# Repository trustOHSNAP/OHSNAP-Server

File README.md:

# OHSNAP Server
This is the repository for the OHSNAP Server project of the OHSNAP platform. For more information, see the [OHSNAP Wiki][https://www.noisebridge.net/wiki/OHSNAP].

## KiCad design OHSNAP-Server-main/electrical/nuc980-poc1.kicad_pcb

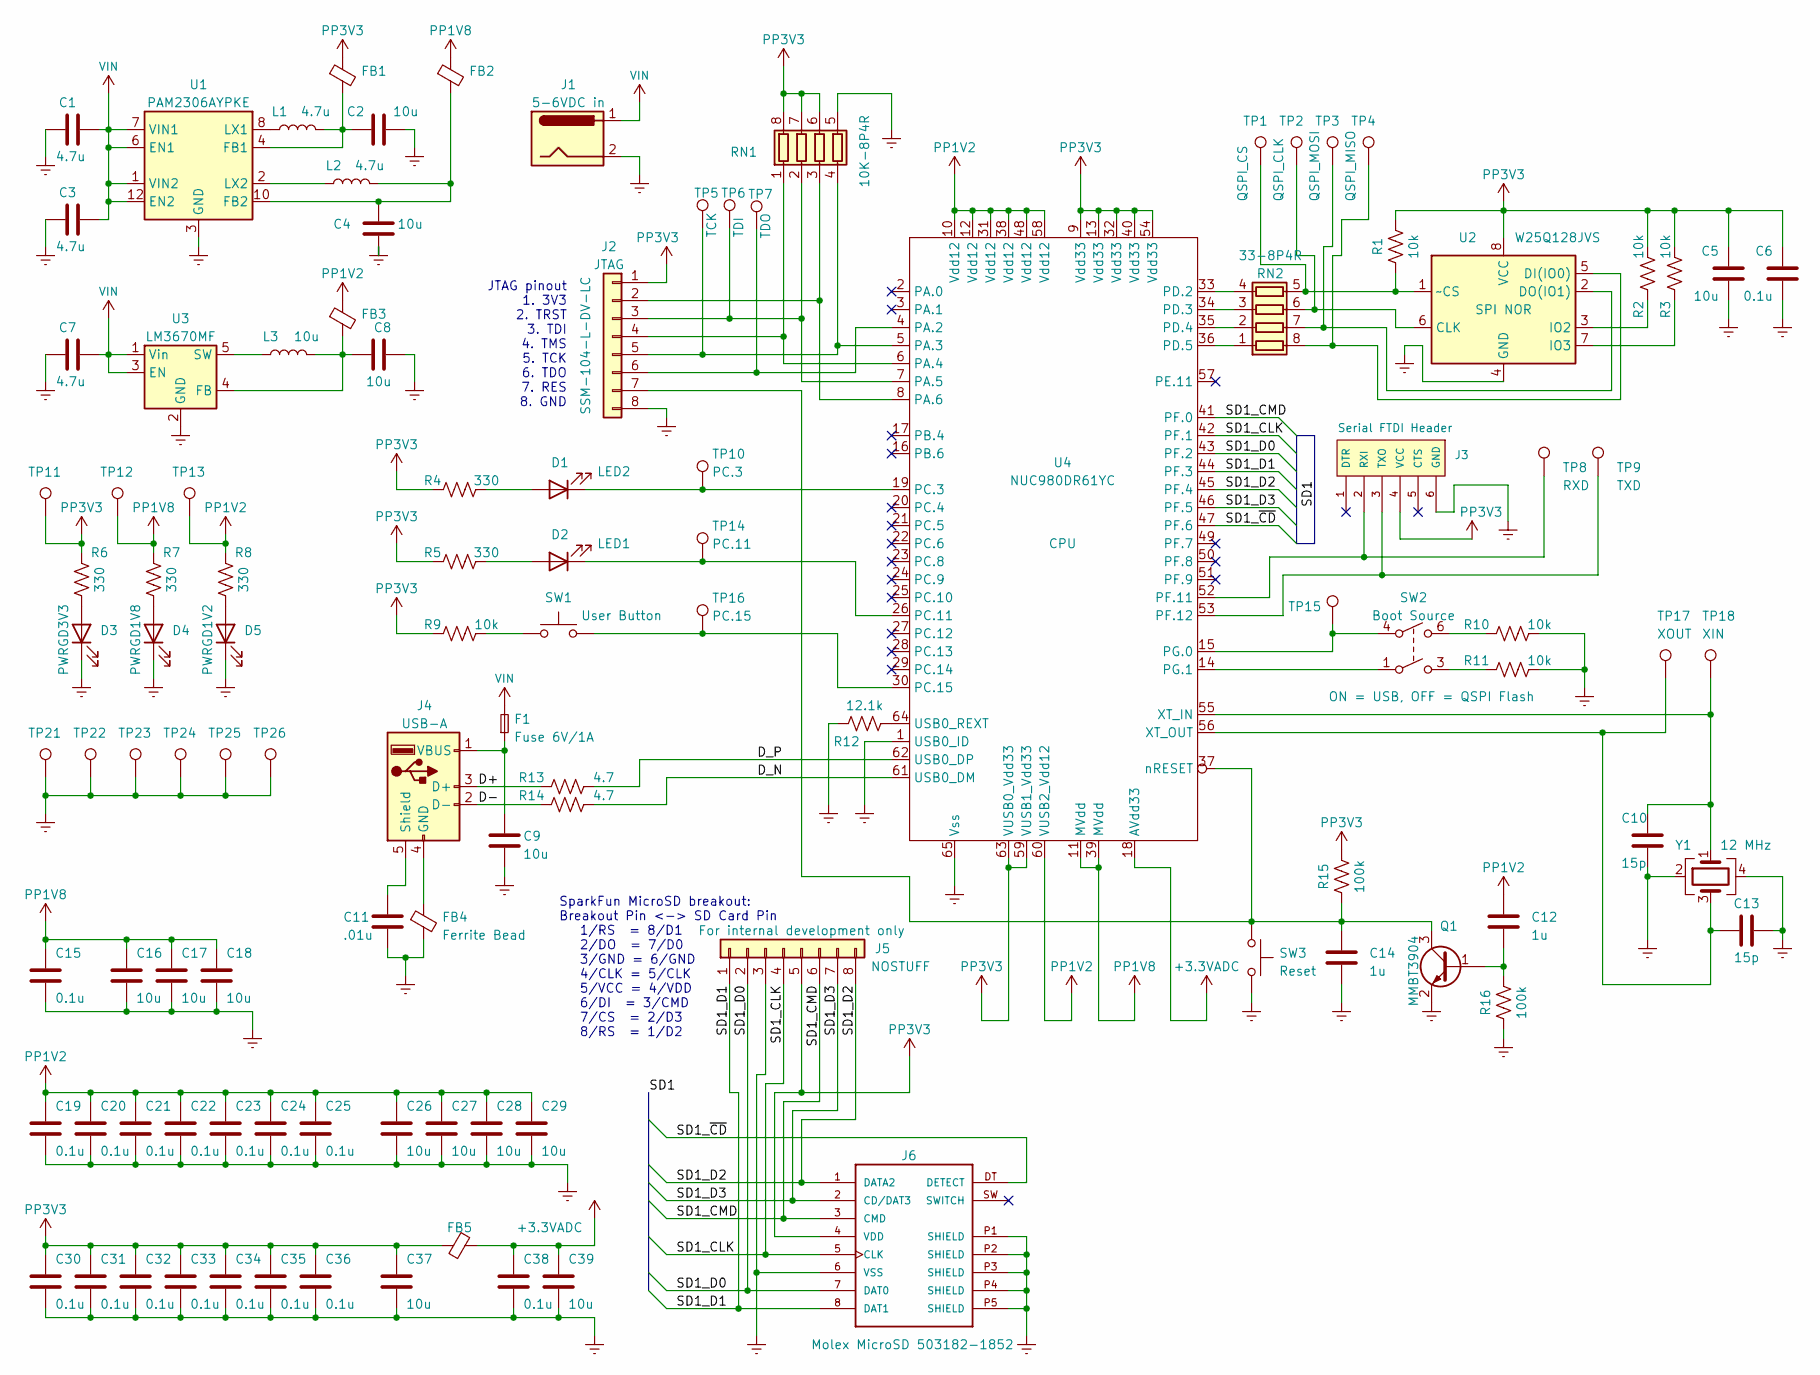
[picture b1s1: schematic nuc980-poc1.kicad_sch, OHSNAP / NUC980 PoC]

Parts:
C1, C3, C7: 4.7u; C_0402_1005Metric
C2, C4, C5, C8, C9, C16, C17, C18, C26, C27, C28, C29, C37, C39: 10u; C_0402_1005Metric
C6, C15, C19, C20, C21, C22, C23, C24, C25, C30, C31, C32, C33, C34, C35, C36, C38: 0.1u; C_0402_1005Metric
C10, C13: 15p; C_0402_1005Metric
C11: .01u; C_0402_1005Metric
C12, C14: 1u; C_0402_1005Metric
D1: LED2; LED_0805_2012Metric
D2: LED1; LED_0805_2012Metric
D3: PWRGD3V3; LED_0805_2012Metric
D4: PWRGD1V8; LED_0805_2012Metric
D5: PWRGD1V2; LED_0805_2012Metric
F1: Fuse 6V/1A; Fuse_1206_3216Metric
FB1, FB2, FB3, FB4, FB5: Ferrite Bead; FB_0603_1608Metric
J1: 5-6VDC in; BarrelJack_CUI_PJ-102AH_Horizontal
J2: JTAG; PinHeader_1x08_P2.54mm_Vertical
J3: Serial FTDI Header; PinHeader_1x06_P2.54mm_Vertical
J4: USB-A; USB_B_OST_USB-B1HSxx_Horizontal
J5: Conn_01x08; PinHeader_1x08_P2.54mm_Vertical
J6: Molex MicroSD 503182-1852; MOLEX_503182-1852
L1, L2: 4.7u; L_0805_2012Metric
L3: 10u; L_0805_2012Metric
Q1: MMBT3904; SOT-23
R1, R2, R3, R9, R10, R11: 10k; R_0603_1608Metric
R4, R5, R6, R7, R8: 330; R_0603_1608Metric
R12: 12.1k; R_0603_1608Metric
R13, R14: 4.7; R_0603_1608Metric
R15, R16: 100k; R_0603_1608Metric
RN1: 10K-8P4R; R_Array_Convex_4x1206
RN2: 33-8P4R; R_Array_Convex_4x1206
SW1: User Button; SW_TH_Tactile_CIT-NC-Series-SPST
SW2: Boot Source; SW_NKK_GW12LJP
SW3: Reset; SW_TH_Tactile_CIT-NC-Series-SPST
TP1: QSPI_CS; TestPoint_Loop_D2.60mm_Drill1.6mm_Beaded
TP2: QSPI_CLK; TestPoint_Loop_D2.60mm_Drill1.6mm_Beaded
TP3: QSPI_MOSI; TestPoint_Loop_D2.60mm_Drill1.6mm_Beaded
TP4: QSPI_MISO; TestPoint_Loop_D2.60mm_Drill1.6mm_Beaded
TP5: TCK; TestPoint_Loop_D2.60mm_Drill1.6mm_Beaded
TP6: TDI; TestPoint_Loop_D2.60mm_Drill1.6mm_Beaded
TP7: TDO; TestPoint_Loop_D2.60mm_Drill1.6mm_Beaded
TP8: RXD; TestPoint_Loop_D2.60mm_Drill1.6mm_Beaded
TP9: TXD; TestPoint_Loop_D2.60mm_Drill1.6mm_Beaded
TP10: PC.3; TestPoint_Loop_D2.60mm_Drill1.6mm_Beaded
TP11: PP3V3; TestPoint_Loop_D2.60mm_Drill1.6mm_Beaded
TP12: PP1V8; TestPoint_Loop_D2.60mm_Drill1.6mm_Beaded
TP13: PP1V2; TestPoint_Loop_D2.60mm_Drill1.6mm_Beaded
TP14: PC.11; TestPoint_Loop_D2.60mm_Drill1.6mm_Beaded
TP15: BOOT; TestPoint_Loop_D2.60mm_Drill1.6mm_Beaded
TP16: PC.15; TestPoint_Loop_D2.60mm_Drill1.6mm_Beaded
TP17: XOUT; TestPoint_Loop_D2.60mm_Drill1.6mm_Beaded
TP18: XIN; TestPoint_Loop_D2.60mm_Drill1.6mm_Beaded
TP21, TP22, TP23, TP24, TP25, TP26: GND; TestPoint_Loop_D2.60mm_Drill1.6mm_Beaded
U1: PAM2306AYPKE; WDFN-12-1EP_3x3mm_P0.45mm_EP1.7x2.5mm
U2: W25Q128JVS; SOIC-8_5.23x5.23mm_P1.27mm
U3: LM3670MF; SOT-23-5
U4: NUC980DR61YC; LQFP-64-1EP_10x10mm_P0.5mm_EP5x5mm
Y1: 12 MHz; Crystal_SMD_EuroQuartz_MJ-4Pin_5.0x3.2mm

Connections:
+1V2: C12.1, C19.1, C20.1, C21.1, C22.1, C23.1, C24.1, C25.1, C26.1, C27.1, C28.1, C29.1, FB3.1, R8.2, TP13.1, U4.10 (Vdd12), U4.12 (Vdd12), U4.31 (Vdd12), U4.38 (Vdd12), U4.48 (Vdd12), U4.58 (Vdd12), U4.60 (VUSB2_Vdd12)
+1V8: C15.1, C16.1, C17.1, C18.1, FB2.1, R7.2, TP12.1, U4.11 (MVdd), U4.39 (MVdd)
+3.3VADC: C38.1, C39.1, FB5.2, U4.18 (AVdd33)
+3V3: C5.2, C6.2, C30.1, C31.1, C32.1, C33.1, C34.1, C35.1, C36.1, C37.1, FB1.1, FB5.1, J2.1, J3.4 (VCC), J5.5, J6.4 (VDD), R1.2, R2.2, R3.2, R4.1, R5.1, R6.2, R9.1, R15.2, RN1.6 (R3.2), RN1.7 (R2.2), RN1.8 (R1.2), TP11.1, U2.8 (VCC), U4.9 (Vdd33), U4.13 (Vdd33), U4.32 (Vdd33), U4.40 (Vdd33), U4.54 (Vdd33), U4.59 (VUSB1_Vdd33), U4.63 (VUSB0_Vdd33)
/D+: J4.3 (D+), R13.1
/D-: J4.2 (D-), R14.1
/D_N: R14.2, U4.61 (USB0_DM)
/D_P: R13.2, U4.62 (USB0_DP)
/SD1_CLK: J5.4, J6.5 (CLK), U4.42 (PF.1)
/SD1_CMD: J5.6, J6.3 (CMD), U4.41 (PF.0)
/SD1_D0: J5.2, J6.7 (DAT0), U4.43 (PF.2)
/SD1_D1: J5.1, J6.8 (DAT1), U4.44 (PF.3)
/SD1_D2: J5.8, J6.1 (DATA2), U4.45 (PF.4)
/SD1_D3: J5.7, J6.2 (CD/DAT3), U4.46 (PF.5)
/SD1_~CD: J6.DT (DETECT), U4.47 (PF.6)
Earth: C1.1, C2.2, C3.1, C4.1, C5.1, C6.1, C7.1, C8.2, C9.2, C10.2, C11.2, C13.2, C14.2, C15.2, C16.2, C17.2, C18.2, C19.2, C20.2, C21.2, C22.2, C23.2, C24.2, C25.2, C26.2, C27.2, C28.2, C29.2, C30.2, C31.2, C32.2, C33.2, C34.2, C35.2, C36.2, C37.2, C38.2, C39.2, D3.1 (K), D4.1 (K), D5.1 (K), FB4.2, J1.2, J2.8, J3.6 (GND), J5.3, J6.6 (VSS), J6.P1 (SHIELD), J6.P2 (SHIELD), J6.P3 (SHIELD), J6.P4 (SHIELD), J6.P5 (SHIELD), Q1.2 (E), R10.2, R11.2, R12.1, R16.1, RN1.5 (R4.2), SW3.2, TP21.1, TP22.1, TP23.1, TP24.1, TP25.1, TP26.1, U1.3 (GND), U1.9 (GND), U1.13 (GND), U2.4 (GND), U3.2 (GND), U4.1 (USB0_ID), U4.65 (Vss), Y1.2, Y1.4
unnamed: D1.2 (A), R4.2
unnamed: D1.1 (K), TP10.1, U4.19 (PC.3)
unnamed: D2.2 (A), R5.2
unnamed: D2.1 (K), TP14.1, U4.26 (PC.11)
unnamed: D3.2 (A), R6.1
unnamed: D4.2 (A), R7.1
unnamed: D5.2 (A), R8.1
unnamed: J2.2, RN1.3 (R3.1), U4.8 (PA.6)
unnamed: J2.3, RN1.2 (R2.1), TP6.1, U4.7 (PA.5)
unnamed: J2.4, RN1.1 (R1.1), U4.6 (PA.4)
unnamed: J2.5, RN1.4 (R4.1), TP5.1, U4.5 (PA.3)
unnamed: J2.6, TP7.1, U4.4 (PA.2)
unnamed: C14.1, J2.7, Q1.3 (C), R15.1, SW3.1, U4.37 (nRESET)
unnamed: J3.2 (RXI), TP8.1, U4.52 (PF.11)
unnamed: J3.3 (TXO), TP9.1, U4.53 (PF.12)
unnamed: FB4.1, J4.4 (GND)
unnamed: C11.1, J4.5 (Shield)
unnamed: C9.1, F1.1, J4.1 (VBUS)
unnamed: C12.2, Q1.1 (B), R16.2
unnamed: R9.2, SW1.1
unnamed: R10.1, SW2.6
unnamed: R11.1, SW2.3
unnamed: RN2.1 (R1.1), U4.36 (PD.5)
unnamed: RN2.8 (R1.2), TP4.1, U2.5 (DI(IO0))
unnamed: RN2.2 (R2.1), U4.35 (PD.4)
unnamed: RN2.7 (R2.2), TP3.1, U2.2 (DO(IO1))
unnamed: RN2.3 (R3.1), U4.34 (PD.3)
unnamed: RN2.6 (R3.2), TP2.1, U2.6 (CLK)
unnamed: RN2.4 (R4.1), U4.33 (PD.2)
unnamed: R1.1, RN2.5 (R4.2), TP1.1, U2.1 (~CS)
unnamed: C2.1, FB1.2, L1.2, U1.4 (FB1)
unnamed: C4.2, FB2.2, L2.2, U1.10 (FB2)
unnamed: L1.1, U1.8 (LX1)
unnamed: L2.1, U1.2 (LX2)
unnamed: R2.1, U2.3 (IO2)
unnamed: R3.1, U2.7 (IO3)
unnamed: C8.1, FB3.2, L3.2, U3.4 (FB)
unnamed: L3.1, U3.5 (SW)
unnamed: SW1.2, TP16.1, U4.30 (PC.15)
unnamed: SW2.4, TP15.1, U4.15 (PG.0)
unnamed: SW2.1, U4.14 (PG.1)
unnamed: R12.2, U4.64 (USB0_REXT)
unnamed: C10.1, TP18.1, U4.55 (XT_IN), Y1.1
unnamed: C13.1, TP17.1, U4.56 (XT_OUT), Y1.3
VIN: C1.2, C3.2, C7.2, F1.2, J1.1, U1.1 (VIN2), U1.6 (EN1), U1.7 (VIN1), U1.12 (EN2), U3.1 (Vin), U3.3 (EN)

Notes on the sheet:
SparkFun MicroSD breakout: Breakout Pin <-> SD Card Pin 1/RS = 8/D1 2/DO = 7/D0 3/GND = 6/GND 4/CLK = 5/CLK 5/VCC = 4/VDD 6/DI = 3/CMD 7/CS = 2/D3 8/RS = 1/D2
JTAG pinout 1. 3V3 2. TRST 3. TDI 4. TMS 5. TCK 6. TDO 7. RES 8. GND

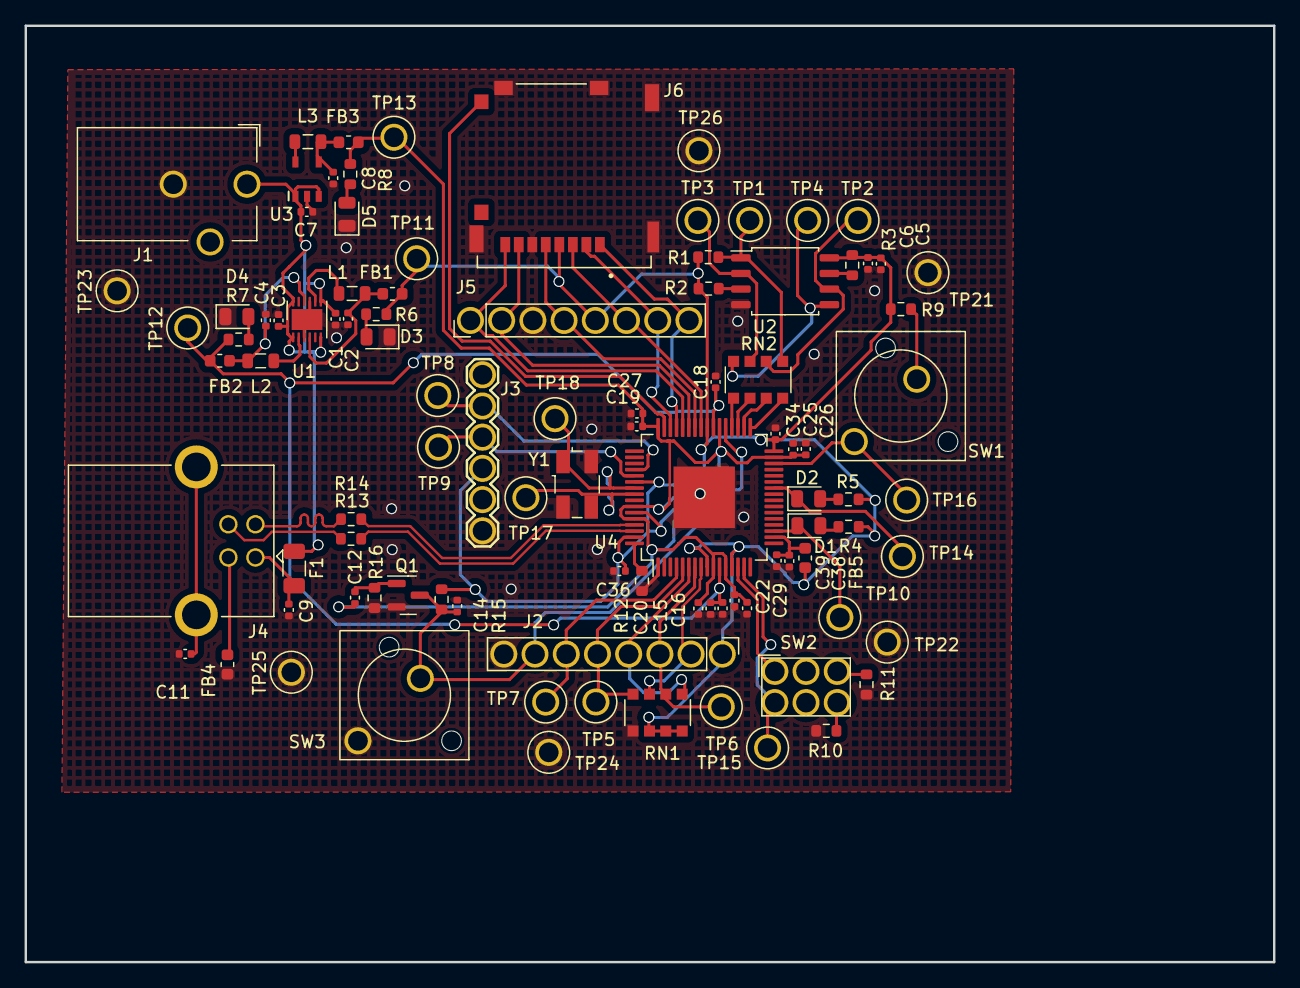
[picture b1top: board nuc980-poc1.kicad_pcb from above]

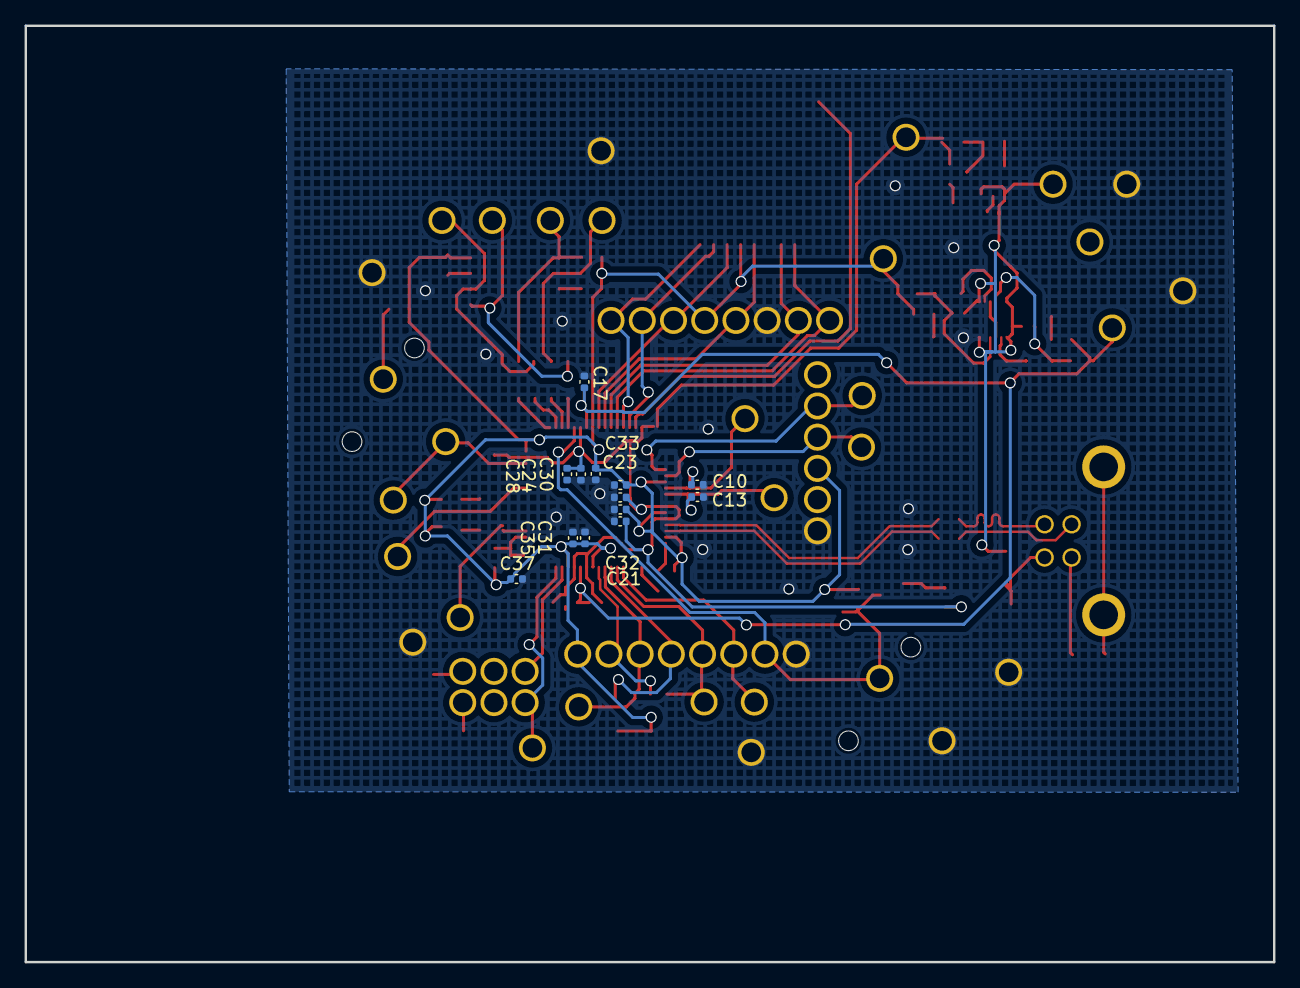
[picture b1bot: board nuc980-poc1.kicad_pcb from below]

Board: 2 copper layers, 101.6 x 76.2 mm, 110 parts (13 on the bottom side), 61 nets.

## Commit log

2021-11-12 Initial repo structure
2021-11-12 Import nuc980-poc1 schematic
2021-12-09 Update schematic to KiCad version 20211123
2021-12-09 Un-ignore CSV files in electrical/ (use for pin assignments tables)
2021-12-09 Add NUC980 pin assignments file
    https://github.com/trustOHSNAP/OHSNAP-Server/issues/4
2022-05-30 Add NUC980 technical documentation
2022-05-30 Partial migration of @iocoder's NUC980 QEMU commits from the old repo
2022-05-31 Add SD card to NUC980 dev board (#3)
2023-08-15 First Revision of PCB Routing
    USB Connector might need updating
2025-07-13 Update to KiCad version 9 (#6)
